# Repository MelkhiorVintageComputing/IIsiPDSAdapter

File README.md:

# PDS Adapter for the Macintosh IIsi

This repository contains recreated PDS adapters for the Macintosh IIsi.

They include a small switch to select the FPU clock, either the CPU clock (20 MHz) or the on-board oscillator (whatever 5V, DIP-8 or DIP-14 oscillator is soldered).

## PLCC

MC68882 FPU tested and working at 20 MHz (system clock)

MC68882 FPU tested and working at 25 MHz (on-board oscillator).

MC68882 FPU tested at 32 MHz, but if the adapter is stand-alone Error 11 occurs when using the FPU. When a [IIsiFPGA](https://github.com/rdolbeau/IIsiFPGA) is plugged in the second slot, 32 MHz seems to work reliably. Current hypothesis is some signal integrity issue when no PDS board is plugged in the adapter.

## PGA

MC68882 FPU tested and working at 20 MHz (system clock)

MC68882 FPU tested and working at 40 MHz (on-board oscillator), using a genuine XC68882RC40

Also known to work at 40 MHz with a IIsiFPGA in the second slot.

## PGA-DUAL

MC68882 FPU tested and working at 20 MHz (system clock) alongside a IIsiFPGA ans IIsiSEthernet, although [with some questions about signal integrity and/or timings](https://68kmla.org/bb/index.php?threads/sethernet-and-sethernet-30-a-new-take-on-pds-ethernet.45888/post-531637).

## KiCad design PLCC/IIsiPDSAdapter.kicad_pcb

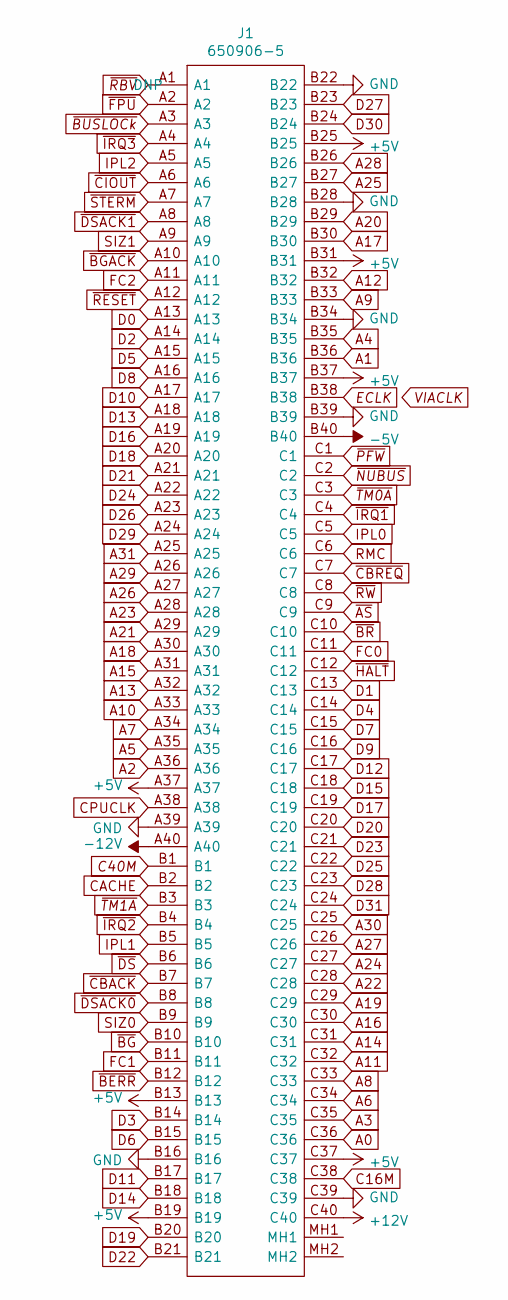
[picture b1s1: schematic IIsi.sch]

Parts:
J1: 650906-5; 6509065; MPN 650906-5

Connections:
+5V: J1.A37, J1.B13, J1.B19, J1.B25, J1.B31, J1.B37, J1.C37; also elsewhere on the board
+12V: J1.C40; also elsewhere on the board
-5V: J1.B40; also elsewhere on the board
-12V: J1.A40; also elsewhere on the board
A0: J1.C36; also elsewhere on the board
A1: J1.B36; also elsewhere on the board
A2: J1.A36; also elsewhere on the board
A3: J1.C35; also elsewhere on the board
A4: J1.B35; also elsewhere on the board
A5: J1.A35; also elsewhere on the board
A6: J1.C34; also elsewhere on the board
A7: J1.A34; also elsewhere on the board
A8: J1.C33; also elsewhere on the board
A9: J1.B33; also elsewhere on the board
A10: J1.A33; also elsewhere on the board
A11: J1.C32; also elsewhere on the board
A12: J1.B32; also elsewhere on the board
A13: J1.A32; also elsewhere on the board
A14: J1.C31; also elsewhere on the board
A15: J1.A31; also elsewhere on the board
A16: J1.C30; also elsewhere on the board
A17: J1.B30; also elsewhere on the board
A18: J1.A30; also elsewhere on the board
A19: J1.C29; also elsewhere on the board
A20: J1.B29; also elsewhere on the board
A21: J1.A29; also elsewhere on the board
A22: J1.C28; also elsewhere on the board
A23: J1.A28; also elsewhere on the board
A24: J1.C27; also elsewhere on the board
A25: J1.B27; also elsewhere on the board
A26: J1.A27; also elsewhere on the board
A27: J1.C26; also elsewhere on the board
A28: J1.B26; also elsewhere on the board
A29: J1.A26; also elsewhere on the board
A30: J1.C25; also elsewhere on the board
A31: J1.A25; also elsewhere on the board
C16M: J1.C38; also elsewhere on the board
C40M: J1.B1; also elsewhere on the board
CACHE: J1.B2; also elsewhere on the board
CPUCLK: J1.A38; also elsewhere on the board
D0: J1.A13; also elsewhere on the board
D1: J1.C13; also elsewhere on the board
D2: J1.A14; also elsewhere on the board
D3: J1.B14; also elsewhere on the board
D4: J1.C14; also elsewhere on the board
D5: J1.A15; also elsewhere on the board
D6: J1.B15; also elsewhere on the board
D7: J1.C15; also elsewhere on the board
D8: J1.A16; also elsewhere on the board
D9: J1.C16; also elsewhere on the board
D10: J1.A17; also elsewhere on the board
D11: J1.B17; also elsewhere on the board
D12: J1.C17; also elsewhere on the board
D13: J1.A18; also elsewhere on the board
D14: J1.B18; also elsewhere on the board
D15: J1.C18; also elsewhere on the board
D16: J1.A19; also elsewhere on the board
D17: J1.C19; also elsewhere on the board
D18: J1.A20; also elsewhere on the board
D19: J1.B20; also elsewhere on the board
D20: J1.C20; also elsewhere on the board
D21: J1.A21; also elsewhere on the board
D22: J1.B21; also elsewhere on the board
D23: J1.C21; also elsewhere on the board
D24: J1.A22; also elsewhere on the board
D25: J1.C22; also elsewhere on the board
D26: J1.A23; also elsewhere on the board
D27: J1.B23; also elsewhere on the board
D28: J1.C23; also elsewhere on the board
D29: J1.A24; also elsewhere on the board
D30: J1.B24; also elsewhere on the board
D31: J1.C24; also elsewhere on the board
ECLK: J1.B38; also elsewhere on the board
FC0: J1.C11; also elsewhere on the board
FC1: J1.B11; also elsewhere on the board
FC2: J1.A11; also elsewhere on the board
GND: J1.A39, J1.B16, J1.B22, J1.B28, J1.B34, J1.B39, J1.C39; also elsewhere on the board
IPL0: J1.C5; also elsewhere on the board
IPL1: J1.B5; also elsewhere on the board
IPL2: J1.A5; also elsewhere on the board
RMC: J1.C6; also elsewhere on the board
SIZ0: J1.B9; also elsewhere on the board
SIZ1: J1.A9; also elsewhere on the board
~AS: J1.C9; also elsewhere on the board
~BERR: J1.B12; also elsewhere on the board
~BG: J1.B10; also elsewhere on the board
~BGACK: J1.A10; also elsewhere on the board
~BR: J1.C10; also elsewhere on the board
~BUSLOCk: J1.A3; also elsewhere on the board
~CBACK: J1.B7; also elsewhere on the board
~CBREQ: J1.C7; also elsewhere on the board
~CIOUT: J1.A6; also elsewhere on the board
~DS: J1.B6; also elsewhere on the board
~DSACK0: J1.B8; also elsewhere on the board
~DSACK1: J1.A8; also elsewhere on the board
~FPU: J1.A2; also elsewhere on the board
~HALT: J1.C12; also elsewhere on the board
~IRQ1: J1.C4; also elsewhere on the board
~IRQ2: J1.B4; also elsewhere on the board
~IRQ3: J1.A4; also elsewhere on the board
~NUBUS: J1.C2; also elsewhere on the board
~PFW: J1.C1; also elsewhere on the board
~RBV: J1.A1; also elsewhere on the board
~RESET: J1.A12; also elsewhere on the board
~RW: J1.C8; also elsewhere on the board
~STERM: J1.A7; also elsewhere on the board
~TM0A: J1.C3; also elsewhere on the board
~TM1A: J1.B3; also elsewhere on the board

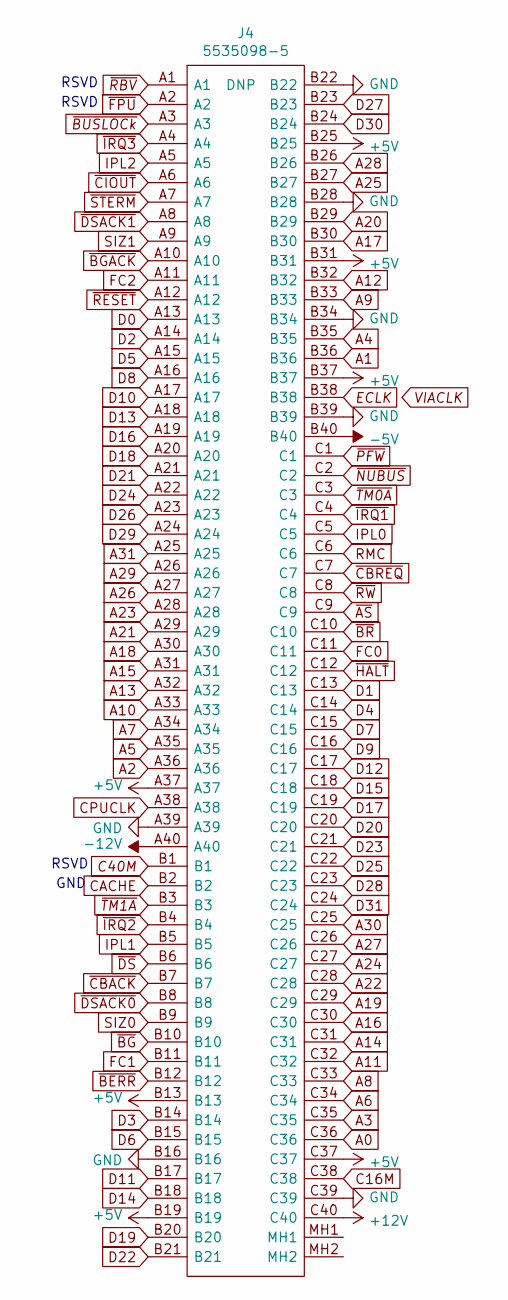
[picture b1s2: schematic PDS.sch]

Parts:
J4: 5535098-5; MPN 5535098-5

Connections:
+5V: J4.A37, J4.B13, J4.B19, J4.B25, J4.B31, J4.B37, J4.C37; also elsewhere on the board
+12V: J4.C40; also elsewhere on the board
-5V: J4.B40; also elsewhere on the board
-12V: J4.A40; also elsewhere on the board
A0: J4.C36; also elsewhere on the board
A1: J4.B36; also elsewhere on the board
A2: J4.A36; also elsewhere on the board
A3: J4.C35; also elsewhere on the board
A4: J4.B35; also elsewhere on the board
A5: J4.A35; also elsewhere on the board
A6: J4.C34; also elsewhere on the board
A7: J4.A34; also elsewhere on the board
A8: J4.C33; also elsewhere on the board
A9: J4.B33; also elsewhere on the board
A10: J4.A33; also elsewhere on the board
A11: J4.C32; also elsewhere on the board
A12: J4.B32; also elsewhere on the board
A13: J4.A32; also elsewhere on the board
A14: J4.C31; also elsewhere on the board
A15: J4.A31; also elsewhere on the board
A16: J4.C30; also elsewhere on the board
A17: J4.B30; also elsewhere on the board
A18: J4.A30; also elsewhere on the board
A19: J4.C29; also elsewhere on the board
A20: J4.B29; also elsewhere on the board
A21: J4.A29; also elsewhere on the board
A22: J4.C28; also elsewhere on the board
A23: J4.A28; also elsewhere on the board
A24: J4.C27; also elsewhere on the board
A25: J4.B27; also elsewhere on the board
A26: J4.A27; also elsewhere on the board
A27: J4.C26; also elsewhere on the board
A28: J4.B26; also elsewhere on the board
A29: J4.A26; also elsewhere on the board
A30: J4.C25; also elsewhere on the board
A31: J4.A25; also elsewhere on the board
C16M: J4.C38; also elsewhere on the board
C40M: J4.B1; also elsewhere on the board
CACHE: J4.B2; also elsewhere on the board
CPUCLK: J4.A38; also elsewhere on the board
D0: J4.A13; also elsewhere on the board
D1: J4.C13; also elsewhere on the board
D2: J4.A14; also elsewhere on the board
D3: J4.B14; also elsewhere on the board
D4: J4.C14; also elsewhere on the board
D5: J4.A15; also elsewhere on the board
D6: J4.B15; also elsewhere on the board
D7: J4.C15; also elsewhere on the board
D8: J4.A16; also elsewhere on the board
D9: J4.C16; also elsewhere on the board
D10: J4.A17; also elsewhere on the board
D11: J4.B17; also elsewhere on the board
D12: J4.C17; also elsewhere on the board
D13: J4.A18; also elsewhere on the board
D14: J4.B18; also elsewhere on the board
D15: J4.C18; also elsewhere on the board
D16: J4.A19; also elsewhere on the board
D17: J4.C19; also elsewhere on the board
D18: J4.A20; also elsewhere on the board
D19: J4.B20; also elsewhere on the board
D20: J4.C20; also elsewhere on the board
D21: J4.A21; also elsewhere on the board
D22: J4.B21; also elsewhere on the board
D23: J4.C21; also elsewhere on the board
D24: J4.A22; also elsewhere on the board
D25: J4.C22; also elsewhere on the board
D26: J4.A23; also elsewhere on the board
D27: J4.B23; also elsewhere on the board
D28: J4.C23; also elsewhere on the board
D29: J4.A24; also elsewhere on the board
D30: J4.B24; also elsewhere on the board
D31: J4.C24; also elsewhere on the board
ECLK: J4.B38; also elsewhere on the board
FC0: J4.C11; also elsewhere on the board
FC1: J4.B11; also elsewhere on the board
FC2: J4.A11; also elsewhere on the board
GND: J4.A39, J4.B16, J4.B22, J4.B28, J4.B34, J4.B39, J4.C39; also elsewhere on the board
IPL0: J4.C5; also elsewhere on the board
IPL1: J4.B5; also elsewhere on the board
IPL2: J4.A5; also elsewhere on the board
RMC: J4.C6; also elsewhere on the board
SIZ0: J4.B9; also elsewhere on the board
SIZ1: J4.A9; also elsewhere on the board
~AS: J4.C9; also elsewhere on the board
~BERR: J4.B12; also elsewhere on the board
~BG: J4.B10; also elsewhere on the board
~BGACK: J4.A10; also elsewhere on the board
~BR: J4.C10; also elsewhere on the board
~BUSLOCk: J4.A3; also elsewhere on the board
~CBACK: J4.B7; also elsewhere on the board
~CBREQ: J4.C7; also elsewhere on the board
~CIOUT: J4.A6; also elsewhere on the board
~DS: J4.B6; also elsewhere on the board
~DSACK0: J4.B8; also elsewhere on the board
~DSACK1: J4.A8; also elsewhere on the board
~FPU: J4.A2; also elsewhere on the board
~HALT: J4.C12; also elsewhere on the board
~IRQ1: J4.C4; also elsewhere on the board
~IRQ2: J4.B4; also elsewhere on the board
~IRQ3: J4.A4; also elsewhere on the board
~NUBUS: J4.C2; also elsewhere on the board
~PFW: J4.C1; also elsewhere on the board
~RBV: J4.A1; also elsewhere on the board
~RESET: J4.A12; also elsewhere on the board
~RW: J4.C8; also elsewhere on the board
~STERM: J4.A7; also elsewhere on the board
~TM0A: J4.C3; also elsewhere on the board
~TM1A: J4.B3; also elsewhere on the board

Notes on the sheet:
GND
RSVD

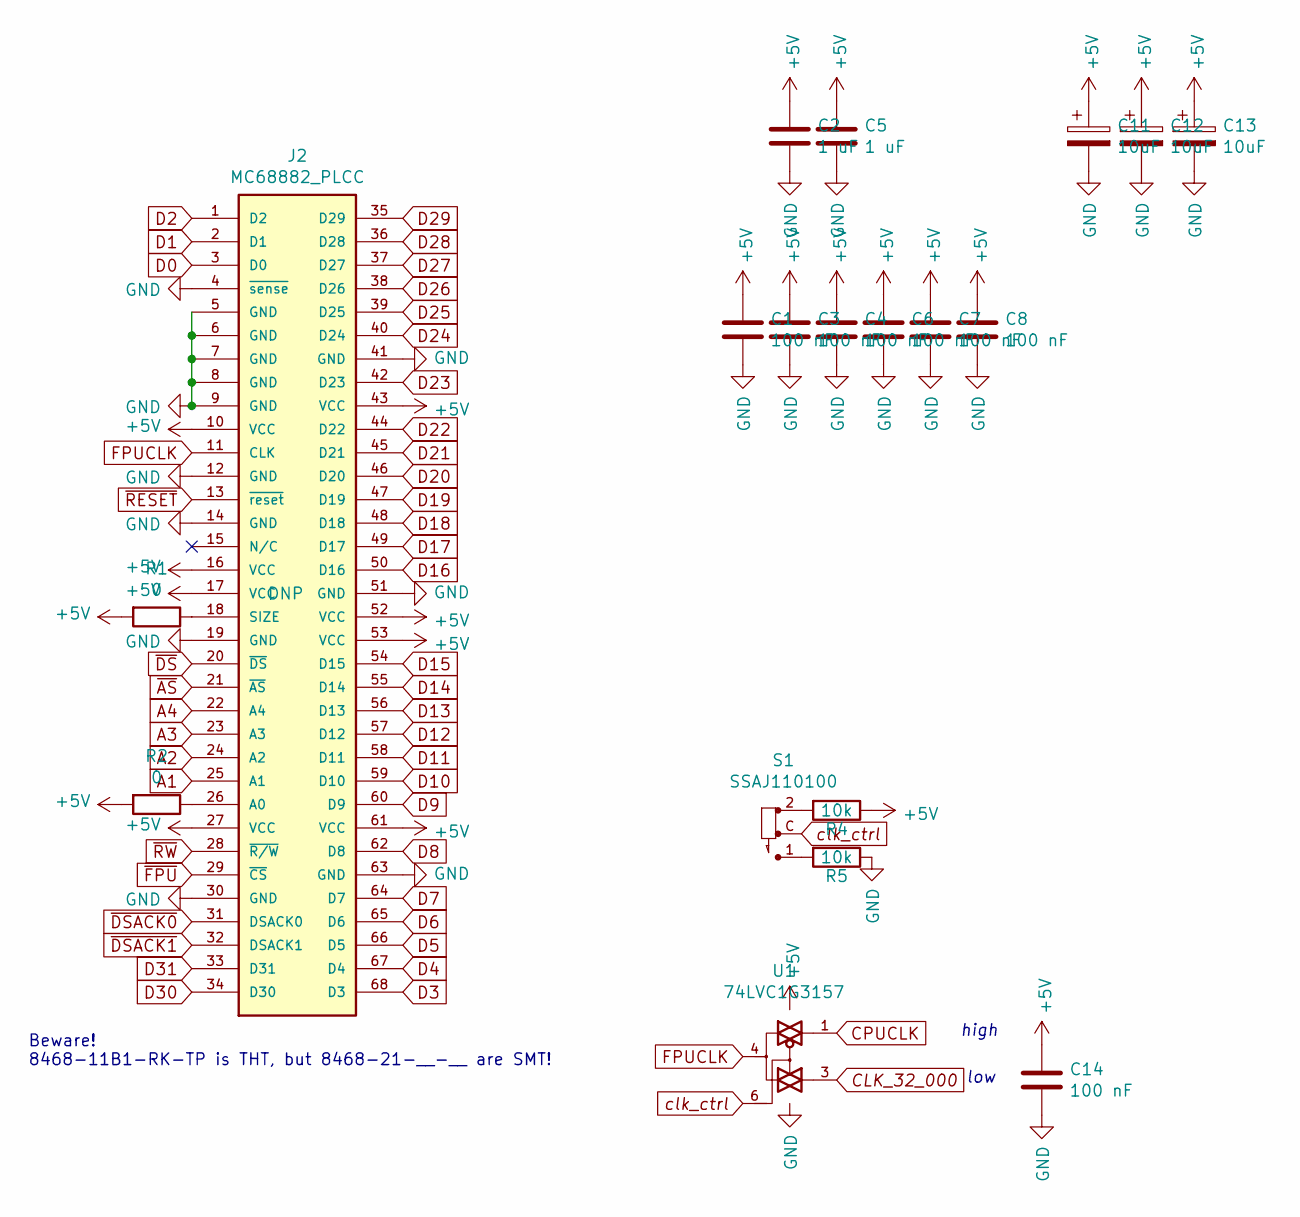
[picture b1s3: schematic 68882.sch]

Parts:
C1, C3, C4, C6, C7, C8, C14: 100 nF; C_0603_1608Metric; MPN CC0603KRX7R9BB104
C2, C5: 1 uF; C_0603_1608Metric; MPN CL10A105KB8NNNC
C11, C12, C13: 10uF; CP_EIA-3216-18_Kemet-A; MPN TAJA106K016RNJ
J2: MC68882_PLCC; 3M_8468-11B1-RK-TP; MPN 8468-11B1-RK-TP; JLCPCB#-ALT C2828041
R1, R2: 0; R_0603_1608Metric; MPN 0603WAF0000T5E
R4, R5: 10k; R_0603_1608Metric; MPN 0603WAF1002T5E
S1: SSAJ110100; SW_SSAJ110100; MPN SSAJ110100
U1: 74LVC1G3157; SOT-23-6; MPN SN74LVC1G3157DBVR

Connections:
+5V: C1.1, C2.1, C3.1, C4.1, C5.1, C6.1, C7.1, C8.1, C11.1, C12.1, C13.1, C14.1, J2.10 (VCC), J2.16 (VCC), J2.17 (VCC), J2.27 (VCC), J2.43 (VCC), J2.52 (VCC), J2.53 (VCC), J2.61 (VCC), R1.2, R2.2, R4.1, U1.5 (VCC); also elsewhere on the board
A1: J2.25 (A1); also elsewhere on the board
A2: J2.24 (A2); also elsewhere on the board
A3: J2.23 (A3); also elsewhere on the board
A4: J2.22 (A4); also elsewhere on the board
CLK_32_000: U1.3; also elsewhere on the board
CPUCLK: U1.1; also elsewhere on the board
D0: J2.3 (D0); also elsewhere on the board
D1: J2.2 (D1); also elsewhere on the board
D2: J2.1 (D2); also elsewhere on the board
D3: J2.68 (D3); also elsewhere on the board
D4: J2.67 (D4); also elsewhere on the board
D5: J2.66 (D5); also elsewhere on the board
D6: J2.65 (D6); also elsewhere on the board
D7: J2.64 (D7); also elsewhere on the board
D8: J2.62 (D8); also elsewhere on the board
D9: J2.60 (D9); also elsewhere on the board
D10: J2.59 (D10); also elsewhere on the board
D11: J2.58 (D11); also elsewhere on the board
D12: J2.57 (D12); also elsewhere on the board
D13: J2.56 (D13); also elsewhere on the board
D14: J2.55 (D14); also elsewhere on the board
D15: J2.54 (D15); also elsewhere on the board
D16: J2.50 (D16); also elsewhere on the board
D17: J2.49 (D17); also elsewhere on the board
D18: J2.48 (D18); also elsewhere on the board
D19: J2.47 (D19); also elsewhere on the board
D20: J2.46 (D20); also elsewhere on the board
D21: J2.45 (D21); also elsewhere on the board
D22: J2.44 (D22); also elsewhere on the board
D23: J2.42 (D23); also elsewhere on the board
D24: J2.40 (D24); also elsewhere on the board
D25: J2.39 (D25); also elsewhere on the board
D26: J2.38 (D26); also elsewhere on the board
D27: J2.37 (D27); also elsewhere on the board
D28: J2.36 (D28); also elsewhere on the board
D29: J2.35 (D29); also elsewhere on the board
D30: J2.34 (D30); also elsewhere on the board
D31: J2.33 (D31); also elsewhere on the board
FPUCLK: J2.11 (CLK), U1.4
GND: C1.2, C2.2, C3.2, C4.2, C5.2, C6.2, C7.2, C8.2, C11.2, C12.2, C13.2, C14.2, J2.4 (~sense), J2.5 (GND), J2.6 (GND), J2.7 (GND), J2.8 (GND), J2.9 (GND), J2.12 (GND), J2.14 (GND), J2.19 (GND), J2.30 (GND), J2.41 (GND), J2.51 (GND), J2.63 (GND), R5.1, U1.2 (GND); also elsewhere on the board
unnamed: J2.18 (SIZE), R1.1
unnamed: J2.26 (A0), R2.1
unnamed: R4.2, S1.2
unnamed: R5.2, S1.1
clk_ctrl: S1.C, U1.6
~AS: J2.21 (~AS); also elsewhere on the board
~DS: J2.20 (~DS); also elsewhere on the board
~DSACK0: J2.31 (DSACK0); also elsewhere on the board
~DSACK1: J2.32 (DSACK1); also elsewhere on the board
~FPU: J2.29 (~CS); also elsewhere on the board
~RESET: J2.13 (~reset); also elsewhere on the board
~RW: J2.28 (~R/W); also elsewhere on the board

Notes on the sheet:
low
high
Beware! 8468-11B1-RK-TP is THT, but 8468-21-__-__ are SMT!

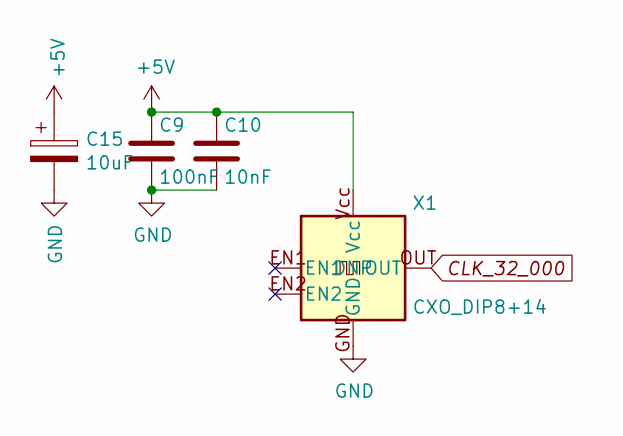
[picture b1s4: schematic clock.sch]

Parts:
C11: 100nF; C_0603_1608Metric; MPN CC0603KRX7R9BB104; Mouser 603-CC603KRX7R8BB104
C13: 10nF; C_0603_1608Metric; MPN 0603B103K500NT; Mouser 603-CC603KRX7R8BB103
C15: 10uF; CP_EIA-3216-18_Kemet-A; MPN TAJA106K016RNJ
X1: CXO_DIP8+14

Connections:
+5V: C11.1, C13.1, C15.1, X1.Vcc; also elsewhere on the board
CLK_32_000: X1.OUT; also elsewhere on the board
GND: C11.2, C13.2, C15.2, X1.GND; also elsewhere on the board

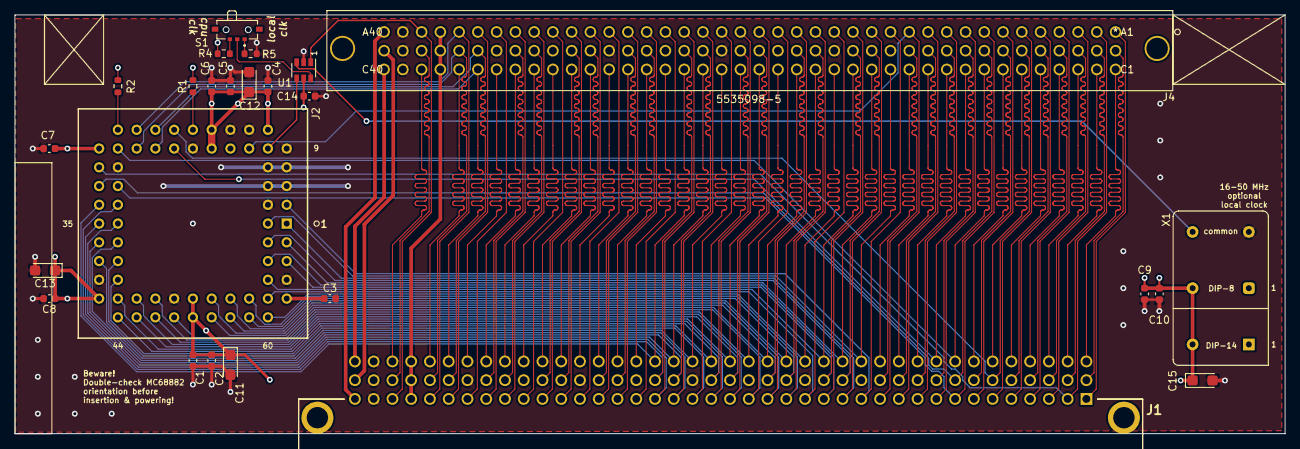
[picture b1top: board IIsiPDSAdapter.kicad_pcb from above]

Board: 4 copper layers, 172.0 x 56.7 mm, 25 parts (0 on the bottom side), 115 nets.

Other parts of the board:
C9: 100nF; C_0603_1608Metric
C10: 10nF; C_0603_1608Metric

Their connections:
+5V: C9.1, C10.1; also elsewhere on the board
GND: C9.2, C10.2; also elsewhere on the board

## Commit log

2023-04-25 initial import
2023-04-26 readme
2023-05-01 PGA draft
2023-05-01 cleanup
2023-05-01 minor fixes
2023-05-03 clean/upd
2023-05-08 drop useless dir
2024-01-08 push dual, completely untested!
2024-04-10 clean-up
2024-05-05 PDS-DUAL built and somewhat tested

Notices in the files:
parts and their libraries:
Copyright 2021 Accelerated Designs. All rights reserved.
